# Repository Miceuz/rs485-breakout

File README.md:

# rs485-breakout
A tiny development board to quickly prototype RS485/Modbus devices

When building RS485/Modbus networks I have identified a need for a platform that would allow me to put various additional sensors or actuators on the network. Like relays to switch stuff, temperature, humidity sensors or other devices that don't have a native Modbus interface.

This board allows interfacing to different digital busses or analog devices.

## Features

* Robust RS485 interface
* ESD protection
* Extendable Modbus slave firmware
* I2C interface
* SPI interface
* 2 analog inputs
* PWM outputs
* 2x5 0.1' prototyping area
* Small form factor allowing PCB integration or inline integration into cable assembly

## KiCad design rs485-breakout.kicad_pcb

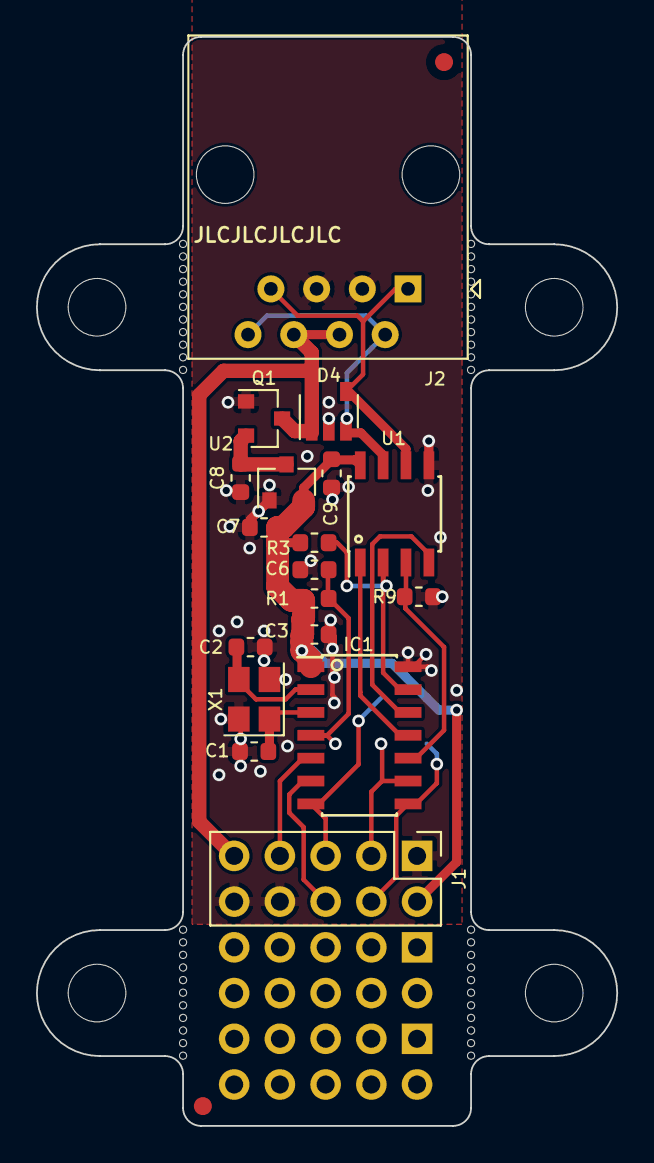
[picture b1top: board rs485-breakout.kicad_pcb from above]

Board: 2 copper layers, 32.2 x 60.5 mm, 27 parts (1 on the bottom side), 18 nets.

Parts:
C1, C2: 13p; C_0603_1608Metric
C3, C6, C7, C8, C9: 1u; C_0603_1608Metric
D4: NUP4004M5T1G; SOT-23-5
FID1, FID2: Fiducial; Fiducial_1mm_Dia_2mm_Outer
H1, H2, H3, H4: MountingHole; MountingHole_3.2mm_M3
IC1: ATTINY441-SSU; SOIC-14_3.9x8.7mm_Pitch1.27mm
J1, J3, J4: Conn_01x08; Pin_Header_Straight_2x05_Pitch2.54mm
J2: RJ45; RJ45_Amphenol_54602-x08_Horizontal
P1: CONN_02X03; Pin_Header_Straight_2x03
Q1: Q_PMOS_GSD; SOT-23
R1, R3, R9: 10k; R_0603_1608Metric
U1: SN65HVD72; SOIC-8_3.9x4.9mm_Pitch1.27mm
U2: MCP1702; SOT-23
X1: 16MHz; Crystal_SMD_3225-4pin_3.2x2.5mm

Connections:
+3V3: C3.1, C7.1, C9.1, IC1.1, J1.2, P1.2, R1.2, R3.1, U1.8, U2.2
/ADC7/OC2B: IC1.6, J1.6
/ADC8/OC2A: IC1.5, J1.7
/MISO: IC1.8, J1.4, P1.1
/MOSI/SDA: IC1.7, J1.5, P1.4
/RESET: C6.1, IC1.4, P1.5, R1.1
/RS485A: D4.4, J2.1, J2.7, U1.6
/RS485B: D4.3, J2.2, J2.8, U1.7
/RS485_DRIVER_ENABLE: IC1.10, R9.1, U1.3
/RX: IC1.11, U1.1
/SCK/SCL: IC1.9, J1.3, P1.3
/TX: IC1.12, U1.4
/~RS485_READER_ENABLE: IC1.13, R3.2, U1.2
GND: C1.2, C2.2, C3.2, C6.2, C7.2, C8.2, C9.2, D4.2, IC1.14, J1.1, J1.8, J1.10, J2.3, J2.5, P1.6, Q1.1, R9.2, U1.5, U2.1, X1.2, X1.4
unnamed: C1.1, IC1.3, X1.1
unnamed: C2.1, IC1.2, X1.3
unnamed: C8.1, Q1.2, U2.3
VCC: D4.1, D4.5, J1.9, J2.4, J2.6, Q1.3

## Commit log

2020-03-22 Initial commit - v1.0 PCB is almost ready for production
2020-03-22 Add basic intro information
2020-03-22 Fix english a bit
2020-03-22 Update version numbers in schematics and PCB meta info
2020-05-20 Add basic firmware skeleton
2020-06-18 Update fuses - higher BOD level and don't output clock on a pin
2020-06-18 Add dummy input register so that soil moisture library can read the fw number corectly
2020-06-18 Don't disable digital buffer on ADC8D as that disables UART (woot? silicon errata?)
2020-07-28 Add ADC8 channel as a holding register
2020-07-28 fix programming header silkscreen
2020-07-28 Add GPIO controll register
2020-07-28 Pass input registers explicitely by reference as that is not the case any more after the compiler change.
2020-07-28 Add a test utility
2021-03-09 Move to a bigger, 8k chip. Add libraries to read sht25 and dps310 sensors via software i2c master. Disable sleep and baudrate,parity,measurement interval update functionality
2021-03-10 Add sense functionality
